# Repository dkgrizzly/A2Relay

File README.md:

> [!WARNING]
> This design is currently untested as of 5/26/2026. There may be errors in the design or example code.
> 
> Update 6/12/2026: Because the 74_259 resets to all outputs low and the relay module is active low, all the relays default to being on at startup.
> Adding a 74_240 inline between the 74_259 and relay board will correct for this in a future revision.
> 
> Schematics and Gerbers for an "OOPS! Inverter" board will be uploaded soon.

> [!CAUTION]
> It is advisable to remove the VCC jumper on the relay board and power the relays with the GND and JD-VCC pin.
> The game port is designed to provide a maximum of 100ma, and with all relays turned on more than 500ma load will be present.

# Apple II Gameport Relay Interface

This is a design for a small PCB to control inexpensive [8-relay modules](https://amzn.to/4dw5lLv) <sup>(Amazon affiliate link)</sup> using the Apple II's gameport annunciators and strobe output.
Use AN3 to set on/off state, AN0-AN2 to select which relay to control, and $C040 strobe to store the value.
All pins are passed through to a socket where you can attach a gamepad, paddles, or other input device.

# Applesoft BASIC Example
```
10 REM To turn on the first relay:
20 PEEK -16295 : REM Clear AN0 $C059
30 PEEK -16293 : REM Clear AN1 $C05B
40 PEEK -16291 : REM Clear AN2 $C05D
50 PEEK -16290 : REM  Set  AN3 $C05E
60 PEEK -16320 : REM Strobe    $C040
```

# 6502 ASM Example
```
0300  lda $C059 ; Clear AN0
0303  lda $C05B ; Clear AN1
0306  lda $C05D ; Clear AN2
0309  lda $C05E ;  Set  AN3
030c  lda $C040 ; Strobe
030f  rts
```

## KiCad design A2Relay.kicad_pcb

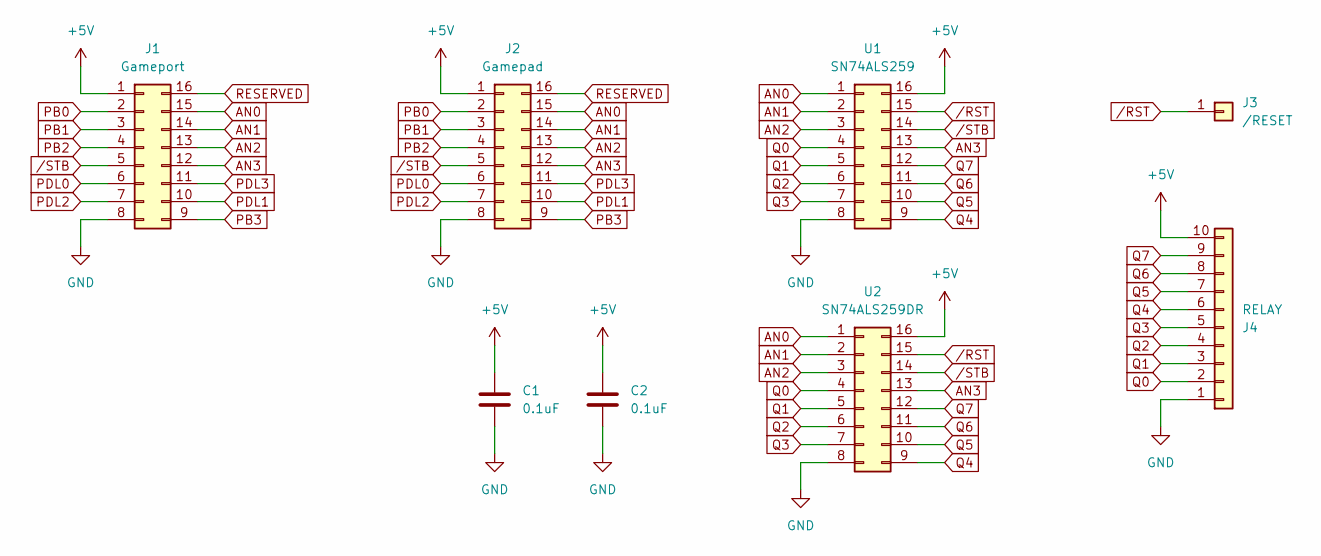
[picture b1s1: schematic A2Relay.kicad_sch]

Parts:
C1: 0.1uF; C_Disc_D4.3mm_W1.9mm_P5.00mm
C2: 0.1uF; C_0603_1608Metric_Pad1.08x0.95mm_HandSolder
J1: Gameport; DIP-16_W7.62mm_Socket
J2: Gamepad; DIP-16_W7.62mm
J3: /RESET; PinHeader_1x01_P2.54mm_Vertical
J4: RELAY; PinHeader_1x10_P2.54mm_Vertical
U1: SN74ALS259; DIP-16_W7.62mm
U2: SN74ALS259DR; SOIC-16_3.9x9.9mm_P1.27mm

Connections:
+5V: C1.1, C2.1, J1.1, J2.1, J4.10, U1.16, U2.16
AN0: J1.15, J2.15, U1.1, U2.1
AN1: J1.14, J2.14, U1.2, U2.2
AN2: J1.13, J2.13, U1.3, U2.3
AN3: J1.12, J2.12, U1.13, U2.13
GND: C1.2, C2.2, J1.8, J2.8, J4.1, U1.8, U2.8
PB0: J1.2, J2.2
PB1: J1.3, J2.3
PB2: J1.4, J2.4
PB3: J1.9, J2.9
PDL0: J1.6, J2.6
PDL1: J1.10, J2.10
PDL2: J1.7, J2.7
PDL3: J1.11, J2.11
Q0: J4.2, U1.4, U2.4
Q1: J4.3, U1.5, U2.5
Q2: J4.4, U1.6, U2.6
Q3: J4.5, U1.7, U2.7
Q4: J4.6, U1.9, U2.9
Q5: J4.7, U1.10, U2.10
Q6: J4.8, U1.11, U2.11
Q7: J4.9, U1.12, U2.12
RESERVED: J1.16, J2.16
/RST: J3.1, U1.15, U2.15
/STB: J1.5, J2.5, U1.14, U2.14

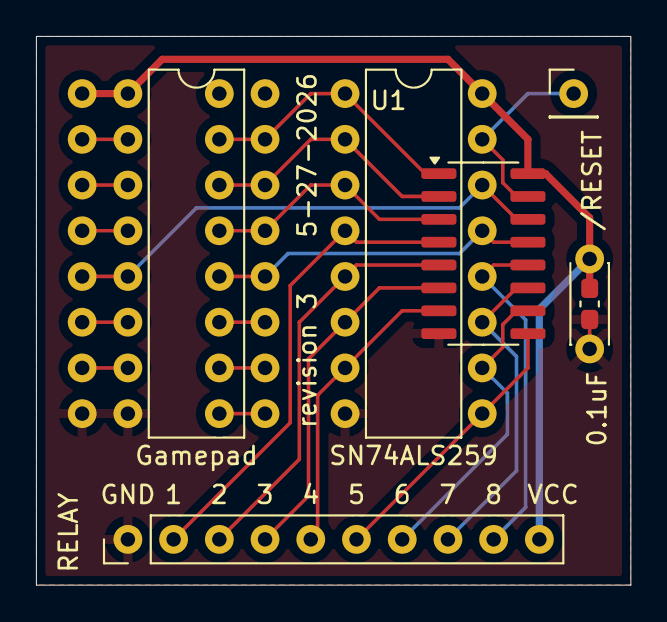
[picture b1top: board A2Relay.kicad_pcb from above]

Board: 2 copper layers, 33.0 x 30.5 mm, 8 parts (0 on the bottom side), 25 nets.

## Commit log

2026-05-26 Update README with description, warnings and examples
    Add description, warnings and usage examples for relay interface
2026-05-26 Add PCB Render
2026-05-26 Update to KiCad 9.0, add surface mount capacitor, swap VCC / GND on relay connector
2026-05-26 Updated PCB Render
2026-05-27 Removed old drill files
2026-05-28 revision 3 - initial prototype run
2026-06-13 Note about output inversion
    Updated warning about outputs being inverted from what the relay board wants.
2026-06-13 Fix warning message formatting in README.md
2026-06-13 Fix formatting issues in README updates

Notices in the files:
A2Relay.kicad_pcb:
© 2026
